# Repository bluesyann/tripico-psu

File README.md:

<h1 align="center">TriPico PSU</h1>

<p align="center">

</p>

> A 3-channel Raspberry Pi Pico instrument that works as a programmable power supply, bench voltmeter/ammeter, and YAML-driven curve tracer all in one.

---

## ⚡ What Is This?

TriPico PSU is a 3-channel instrument built around a Raspberry Pi Pico and dual INA3221 measurement ICs. It can be configured as:

- **Programmable multi-channel power supply** — independent voltage/current regulation on 3 channels with max power limits
- **Live voltmeter/ammeter front end** — real-time monitoring with interactive desktop GUI and live charts
- **Curve tracer** — automated characterization of transistors, diodes, and components using YAML recipe automation

### Repository Structure

- **[hardware/README.md](hardware/README.md)** — PCB schematic, PCB layout, front-panel design, and wiring integration
- **[firmware/README.md](firmware/README.md)** — Raspberry Pi Pico firmware (MicroPython async control loop)
- **[software/README.md](software/README.md)** — Host computer application (interactive GUI + YAML automation)

### Picture Insertion Block: Full Build Overview

Use this block when you have a cleaner hero photo than global_view.jpg.

```md

```

---

## 🎯 How It Works

The Pico firmware regulates 3 channels independently, continuously reads voltage/current through dual INA3221 sensors, and streams measurements over serial at 115200 baud. On the computer side, you have two modes:

- **Interactive GUI mode** — real-time control and monitoring with live voltage/current charts
- **YAML automation mode** — scripted sweeps, static test runs, CSV export, and optional plots

---

## 🚀 Build And Run (Step By Step)

### 1) Build The Hardware

### Picture Insertion Block: Build Steps Collage

Add one image showing PCB + panel + enclosure parts before assembly.

```md

```

1. Open the KiCad files and fabricate/assemble the PCB.
2. Build the front panel/enclosure from the provided enclosure assets.
3. Wire the panel elements (switches, relays, connectors, LEDs) to the PCB.

Detailed files and notes are in [hardware/README.md](hardware/README.md).

### 2) Flash The Pico Firmware

### Picture Insertion Block: Pico Flashing

Show your firmware upload workflow or MicroPython file layout.

```md

```

1. Copy all files from the firmware folder to the Pico:
	 - config.py
	 - device.py
	 - ina3221.py
	 - main.py
2. Reboot the board and verify serial output appears.

Firmware details are in [firmware/README.md](firmware/README.md).

### 3) Set Up The Computer Software

### Picture Insertion Block: Software Setup

Optional terminal screenshot after successful dependency install.

```md

```

1. Create a Python virtual environment.
2. Install dependencies from software/requirements.txt.
3. Configure software/tripico-psu_config.yaml for your serial port and calibration folder.

Software details are in [software/README.md](software/README.md).

### 4) Use It

### Picture Insertion Block: First Run

Add one screenshot with the GUI connected and channels active.

```md

```

- GUI mode (interactive bench use):
	- Run software/tripico-psu_gui.py
	- Connect to the Pico
	- Set channel mode (V or mA), setpoint, and max power

- YAML mode (automation and characterization):
	- Run software/tripico-psu_run_yaml.py with one YAML recipe from software/examples
	- Capture sweeps/static runs to CSV and optional plots

---

## 📊 Typical Practical Uses

### Standalone power supply behavior

### Picture Insertion Block: Power Supply Mode

```md

```

- Set channels in voltage or current mode
- Apply max-power protection per channel
- Monitor live values and status (regulation/saturation/alerts)

### Digital voltmeter/ammeter style usage

### Picture Insertion Block: Meter Mode

```md

```

- Use one or more channels as sensing points
- Observe time-series voltage/current in the GUI
- Switch measurement range from the front panel selector

### Curve tracer usage

### Picture Insertion Block: Curve Tracer Plot

```md

```

- Define nested sweeps in YAML (for example transistor curves)
- Plot I-V behavior in real time
- Export data for offline analysis

## Example Screens

- GUI examples:
	- [docs/pictures/gui.png](docs/pictures/gui.png)
	- [docs/pictures/gui2.png](docs/pictures/gui2.png)

## Current Status

This repository already contains working code and build assets. Hardware assembly details are intentionally partial and should be completed with your own wiring/BOM documentation as you finalize your build.

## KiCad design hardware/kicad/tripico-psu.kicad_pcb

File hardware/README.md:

<h1 align="center">Hardware Build Guide</h1>
<p align="center"><strong>PCB + Front Panel + Wiring Integration</strong></p>

# 🏗️ Hardware Build Guide

> PCB design, front-panel enclosure, mechanical integration, and electrical bring-up.

This guide covers the complete hardware design and assembly workflow:

## Picture Insertion Block: Hardware Assembly Overview

```md

```

- **KiCad project** (complete schematic + PCB layout)
- **Front panel enclosure files** (SVG vector artwork + OpenSCAD 3D extrusion script)

This guide is intentionally conservative where assembly details depend on your specific choices (connectors, wiring gauge, fuse ratings, etc.).

## 📋 What Is In This Folder

## Picture Insertion Block: Repository Hardware Assets

```md

```

- kicad/
  - tripico-psu.kicad_sch: electrical schematic
  - tripico-psu.kicad_pcb: PCB layout
  - tripico-psu.kicad_pro and tripico-psu.kicad_prl: project settings

- enclosure/
  - front_panel_inkscape.svg: editable panel design
  - front_panel_polygon.svg: panel path used for extrusion
  - front_panel.scad: OpenSCAD extrusion script

## 🎯 Suggested Physical Architecture

## Picture Insertion Block: Front Panel Layout

```md

```

Based on the files and pictures, the build appears to include:

- A main PCB with one Raspberry Pi Pico and analog/power stages
- Front-panel controls and indicators:
  - Main power switch
  - Range selector for current measurement shunts
  - Push-pull channel enable switches (A/B/C)
  - Channel output terminals
  - Status LEDs and safety indication
- External supply input connector

Use the schematic and PCB net labels as the source of truth for wiring.

## 🔨 Build Workflow

### 1) PCB Fabrication And Assembly

### Picture Insertion Block: PCB Render And Assembled Board

```md

```

1. Open kicad/tripico-psu.kicad_pro in KiCad.
2. Run ERC/DRC and inspect any warnings before fabrication.
3. Generate Gerbers and drill files from the PCB editor.
4. Assemble components according to the schematic and footprints.

### 2) Front Panel Fabrication

### Picture Insertion Block: Panel Fabrication

```md

```

1. Edit enclosure/front_panel_inkscape.svg for labels/hole placement.
2. Use enclosure/front_panel_polygon.svg with OpenSCAD:

```scad
linear_extrude(height = 0.5) import("front_panel_polygon.svg");
```

3. Export for your process (laser/CNC/print) as needed.

### 3) Mechanical Integration

### Picture Insertion Block: Internal Wiring

```md

```

1. Mount PCB in enclosure.
2. Mount panel hardware (switches, jacks, LEDs).
3. Route and secure wiring between panel and PCB connectors.

### 4) Electrical Bring-Up

### Picture Insertion Block: Bring-Up Checklist Bench Setup

```md

```

1. Perform continuity checks before power-on.
2. Bring up with current-limited bench supply first.
3. Verify rails, relay behavior, and panel switch detection.
4. Flash firmware and test serial communication with host software.

## ✅ Wiring Checklist (To Complete)

## Picture Insertion Block: Final Wiring Diagram

```md

```

Use this section as your own integration checklist:

- External power input connector pinout: TODO
- Output terminal mapping for channels A/B/C: TODO
- Panel LED wiring and polarity: TODO
- Push-pull switch wiring reference: TODO
- Range selector switch wiring reference: TODO
- Safety relay coil and contact wiring: TODO
- Fuse/protection devices and ratings: TODO

## ⚠️ Safety Notes

- Use an inline fuse on the external supply input.
- Keep high-current traces/wires short and appropriately sized.
- Verify grounding strategy between analog sensing and power paths.
- Confirm enclosure insulation and strain relief before regular use.

## Assets For Documentation

Project image: docs/pictures/global_view.jpg

You can extend this README with BOM, exact connector references, and final wiring photos as you finalize your hardware revision.

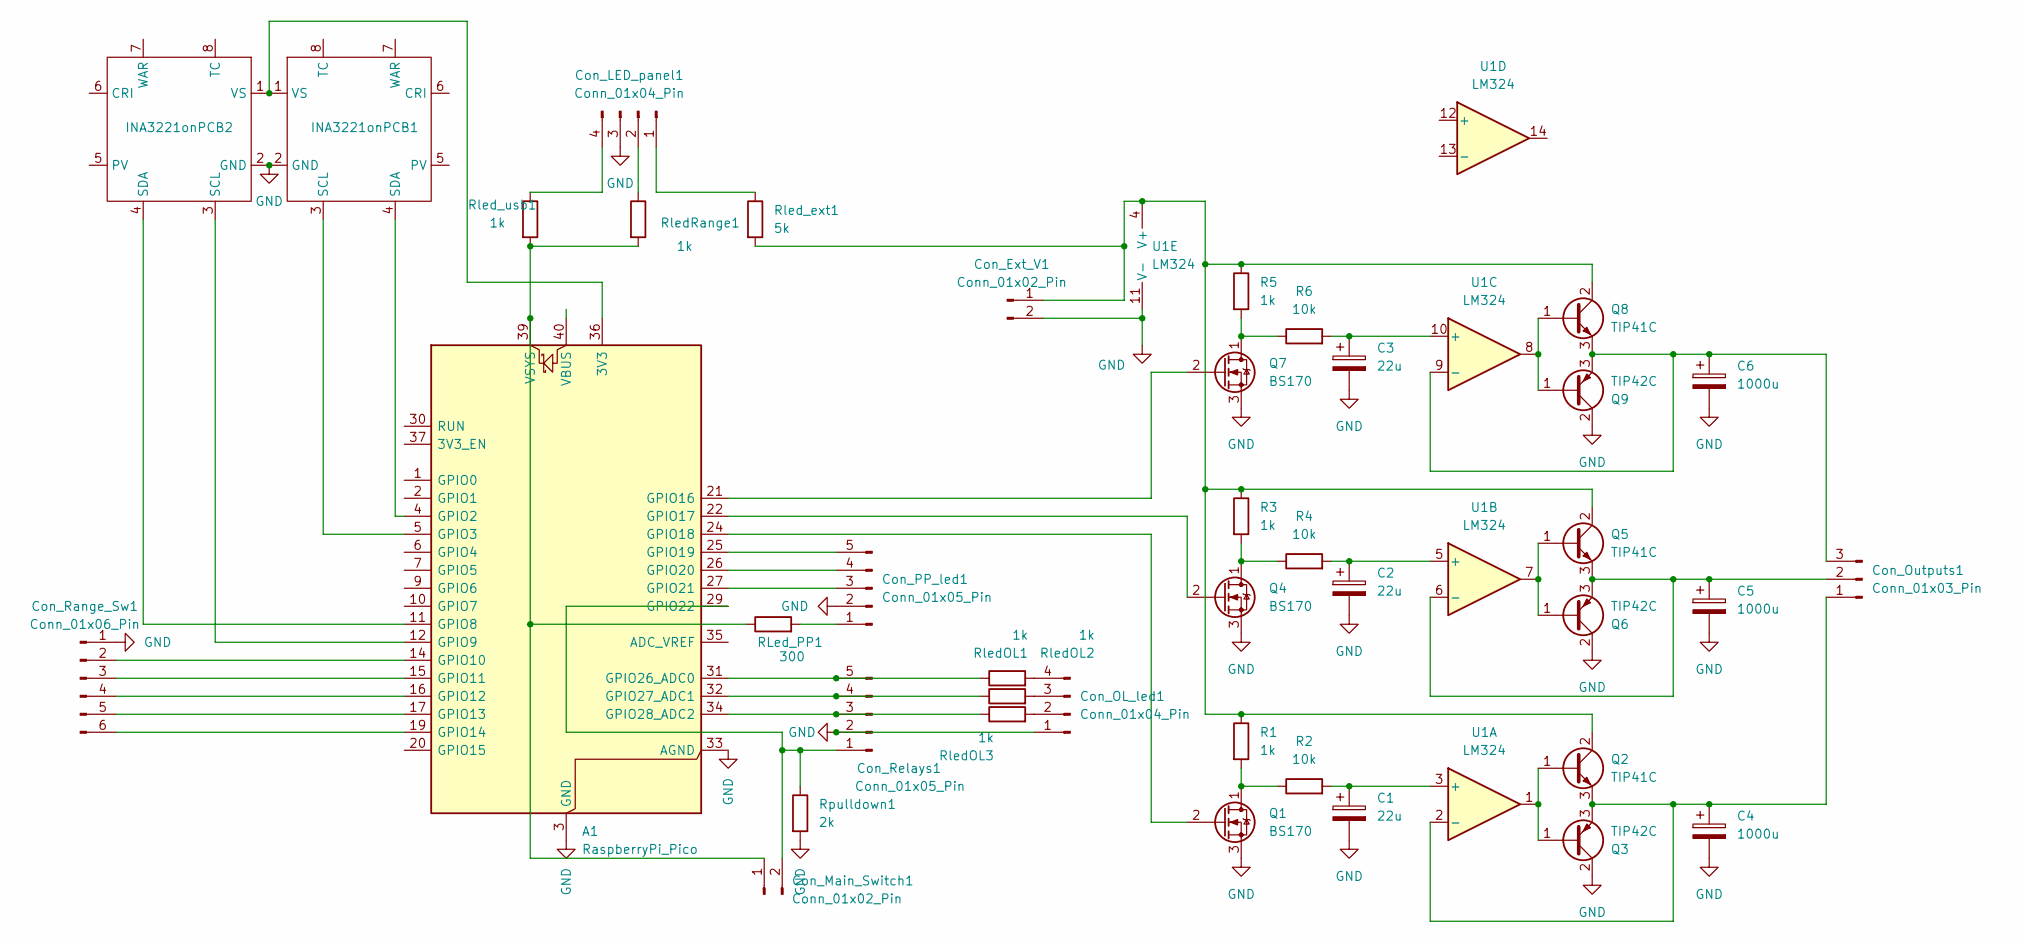
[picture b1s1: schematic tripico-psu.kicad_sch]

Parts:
A1: RaspberryPi_Pico; RaspberryPi_Pico_THT_NoAntenna
C1, C2, C3: 22u; CP_Radial_D5.0mm_P2.00mm
C4, C5, C6: 1000u; CP_Radial_D16.0mm_P7.50mm
Con_Ext_V1: Conn_01x02_Pin; JST_PH_B2B-PH-K_1x02_P2.00mm_Vertical
Con_LED_panel1: Conn_01x04_Pin; JST_PH_B4B-PH-K_1x04_P2.00mm_Vertical
Con_Main_Switch1: Conn_01x02_Pin; JST_PH_B2B-PH-K_1x02_P2.00mm_Vertical
Con_OL_led1: Conn_01x04_Pin; JST_PH_B4B-PH-K_1x04_P2.00mm_Vertical
Con_Outputs1: Conn_01x03_Pin; JST_PH_B3B-PH-K_1x03_P2.00mm_Vertical
Con_PP_led1: Conn_01x05_Pin; JST_PH_B5B-PH-K_1x05_P2.00mm_Vertical
Con_Range_Sw1: Conn_01x06_Pin; JST_PH_B6B-PH-K_1x06_P2.00mm_Vertical
Con_Relays1: Conn_01x05_Pin; JST_PH_B5B-PH-K_1x05_P2.00mm_Vertical
INA3221onPCB1, INA3221onPCB2: INA3221_on_PCB
Q1, Q4, Q7: BS170; TO-92_Inline
Q2, Q5, Q8: TIP41C; TO-220-3_Vertical
Q3, Q6, Q9: TIP42C; TO-220-3_Vertical
R1, R3, R5: 1k; R_Axial_DIN0207_L6.3mm_D2.5mm_P10.16mm_Horizontal
R2, R4, R6: 10k; R_Axial_DIN0207_L6.3mm_D2.5mm_P10.16mm_Horizontal
RLed_PP1: 300; R_Axial_DIN0207_L6.3mm_D2.5mm_P10.16mm_Horizontal
RledOL1, RledOL2, RledOL3: 1k; R_Axial_DIN0207_L6.3mm_D2.5mm_P10.16mm_Horizontal
RledRange1: 1k; R_Axial_DIN0207_L6.3mm_D2.5mm_P10.16mm_Horizontal
Rled_ext1: 5k; R_Axial_DIN0207_L6.3mm_D2.5mm_P10.16mm_Horizontal
Rled_usb1: 1k; R_Axial_DIN0207_L6.3mm_D2.5mm_P10.16mm_Horizontal
Rpulldown1: 2k; R_Axial_DIN0207_L6.3mm_D2.5mm_P2.54mm_Vertical
U1: LM324; DIP-14_W7.62mm_Socket_LongPads

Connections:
GND: A1.3 (GND), A1.8 (GND), A1.13 (GND), A1.18 (GND), A1.23 (GND), A1.28 (GND), A1.33 (AGND), A1.38 (GND), C1.2, C2.2, C3.2, C4.2, C5.2, C6.2, Con_Ext_V1.2, Con_LED_panel1.3, Con_OL_led1.1, Con_PP_led1.2, Con_Range_Sw1.1, Con_Relays1.2, INA3221onPCB1.2 (GND), INA3221onPCB2.2 (GND), Q1.3 (S), Q3.2 (C), Q4.3 (S), Q6.2 (C), Q7.3 (S), Q9.2 (C), Rpulldown1.2, U1.11 (V-)
unnamed: A1.36 (3V3), INA3221onPCB1.1 (VS), INA3221onPCB2.1 (VS)
unnamed: A1.4 (GPIO2), INA3221onPCB1.4 (SDA)
unnamed: A1.5 (GPIO3), INA3221onPCB1.3 (SCL)
unnamed: A1.11 (GPIO8), INA3221onPCB2.4 (SDA)
unnamed: A1.12 (GPIO9), INA3221onPCB2.3 (SCL)
unnamed: A1.14 (GPIO10), Con_Range_Sw1.2
unnamed: A1.15 (GPIO11), Con_Range_Sw1.3
unnamed: A1.16 (GPIO12), Con_Range_Sw1.4
unnamed: A1.17 (GPIO13), Con_Range_Sw1.5
unnamed: A1.19 (GPIO14), Con_Range_Sw1.6
unnamed: A1.21 (GPIO16), Q7.2 (G)
unnamed: A1.22 (GPIO17), Q4.2 (G)
unnamed: A1.24 (GPIO18), Q1.2 (G)
unnamed: A1.25 (GPIO19), Con_PP_led1.5
unnamed: A1.26 (GPIO20), Con_PP_led1.4
unnamed: A1.27 (GPIO21), Con_PP_led1.3
unnamed: A1.29 (GPIO22), Con_Main_Switch1.2, Con_Relays1.1, Rpulldown1.1
unnamed: A1.31 (GPIO26_ADC0), Con_Relays1.5, RledOL1.1
unnamed: A1.32 (GPIO27_ADC1), Con_Relays1.4, RledOL2.1
unnamed: A1.34 (GPIO28_ADC2), Con_Relays1.3, RledOL3.1
unnamed: A1.39 (VSYS), Con_Main_Switch1.1, RLed_PP1.1, RledRange1.2, Rled_usb1.2
unnamed: Con_Ext_V1.1, Q2.2 (C), Q5.2 (C), Q8.2 (C), R1.1, R3.1, R5.1, Rled_ext1.2, U1.4 (V+)
unnamed: Con_LED_panel1.1, Rled_ext1.1
unnamed: Con_LED_panel1.2, RledRange1.1
unnamed: Con_LED_panel1.4, Rled_usb1.1
unnamed: Con_OL_led1.2, RledOL3.2
unnamed: Con_OL_led1.3, RledOL2.2
unnamed: Con_OL_led1.4, RledOL1.2
unnamed: C4.1, Con_Outputs1.1, Q2.3 (E), Q3.3 (E), U1.2 (-)
unnamed: C5.1, Con_Outputs1.2, Q5.3 (E), Q6.3 (E), U1.6 (-)
unnamed: C6.1, Con_Outputs1.3, Q8.3 (E), Q9.3 (E), U1.9 (-)
unnamed: Con_PP_led1.1, RLed_PP1.2
unnamed: Q1.1 (D), R1.2, R2.1
unnamed: Q2.1 (B), Q3.1 (B), U1.1
unnamed: Q4.1 (D), R3.2, R4.1
unnamed: Q5.1 (B), Q6.1 (B), U1.7
unnamed: Q7.1 (D), R5.2, R6.1
unnamed: Q8.1 (B), Q9.1 (B), U1.8
unnamed: C1.1, R2.2, U1.3 (+)
unnamed: C2.1, R4.2, U1.5 (+)
unnamed: C3.1, R6.2, U1.10 (+)

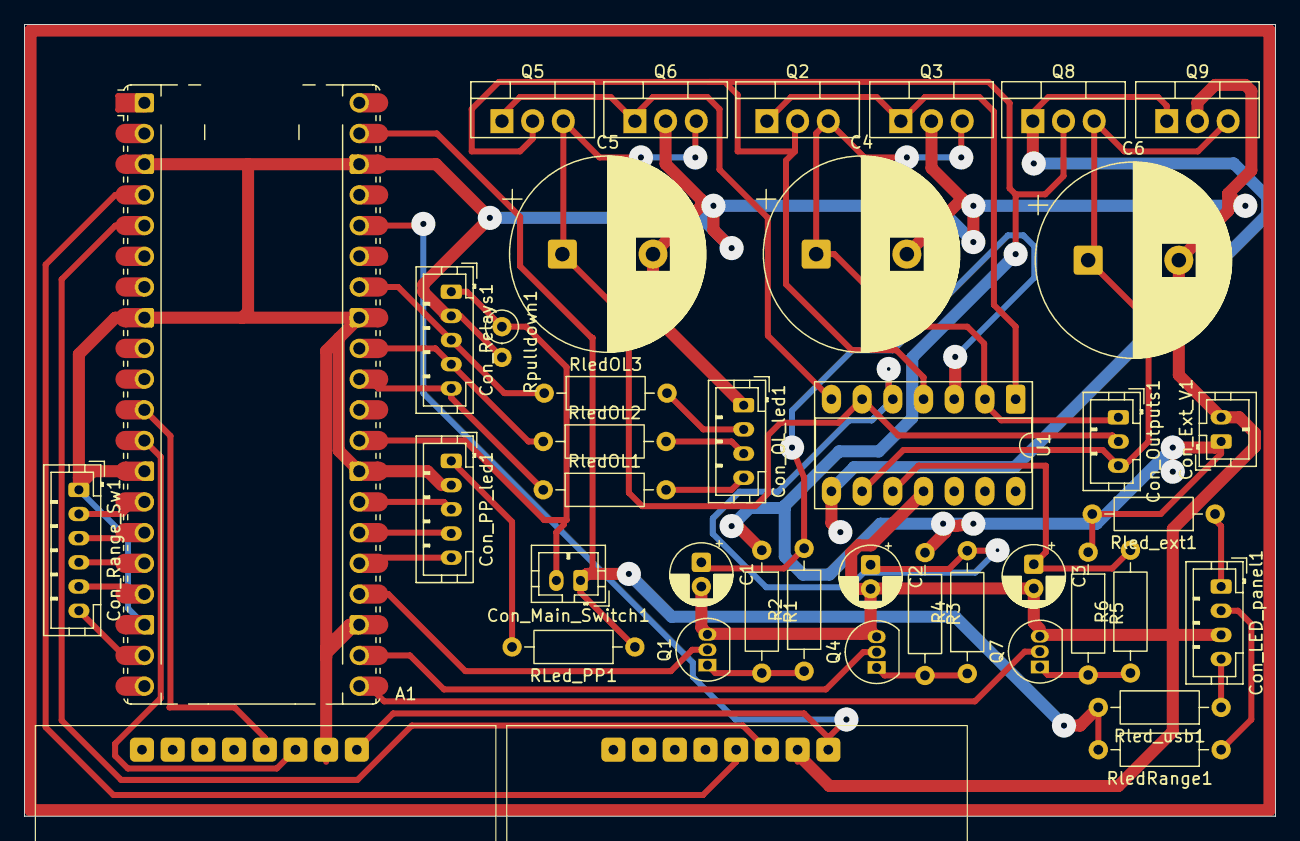
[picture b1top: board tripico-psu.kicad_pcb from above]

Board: 2 copper layers, 103.5 x 65.5 mm, 41 parts (0 on the bottom side), 42 nets.

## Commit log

2026-04-09 bug fixes in gui
2026-04-11 Added documentation
